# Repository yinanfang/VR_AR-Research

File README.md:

# VR_AR-Research
Code repo for VR_AR-Research

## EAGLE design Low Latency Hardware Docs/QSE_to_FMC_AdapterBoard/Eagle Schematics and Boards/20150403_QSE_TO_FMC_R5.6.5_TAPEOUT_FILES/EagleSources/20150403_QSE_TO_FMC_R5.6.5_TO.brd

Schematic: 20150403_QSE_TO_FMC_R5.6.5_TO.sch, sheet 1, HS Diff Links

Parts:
C100, C101: 100nF; CAPC1005X60N; PARTNO GRM155R71C104KA88D
H1, H2, H3, H4: MOUNT-PAD-ROUND3.2; 3,2-PAD; PARTNO *
J101_GBCTCLK1_N, J102-GBCTCLK1_P: SMA-SMD; MPN 132134-10; DIGIKEY_SKU 132134-10-ND
TP5: LOOP0_N; TP08R; PARTNO *
TP6: LOOP0_P; TP08R; PARTNO *
TP7, TP8: GND; TP08R; PARTNO *

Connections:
GBCTCLK1_M2C_C_N: C100.1 (2), J101_GBCTCLK1_N.1
GBCTCLK1_M2C_C_P: C101.1 (2), J102-GBCTCLK1_P.1
GBCTCLK1_M2C_N: C100.2 (1); also elsewhere on the board
GBCTCLK1_M2C_P: C101.2 (1); also elsewhere on the board
GND: H1.B3,2, H2.B3,2, H3.B3,2, H4.B3,2, J101_GBCTCLK1_N.2@1 (2), J101_GBCTCLK1_N.2@2 (2), J101_GBCTCLK1_N.2@3 (2), J101_GBCTCLK1_N.2@4 (2), J101_GBCTCLK1_N.2@5 (2), J101_GBCTCLK1_N.2@6 (2), J102-GBCTCLK1_P.2@1 (2), J102-GBCTCLK1_P.2@2 (2), J102-GBCTCLK1_P.2@3 (2), J102-GBCTCLK1_P.2@4 (2), J102-GBCTCLK1_P.2@5 (2), J102-GBCTCLK1_P.2@6 (2), TP7.TP, TP8.TP; also elsewhere on the board
LOOP0_N: TP5.TP; also elsewhere on the board
LOOP0_P: TP6.TP; also elsewhere on the board

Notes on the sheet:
3.2mm (1/4") mounting holes, tied to ground plane.
V7 Bank 37
V7 Bank 12
V7 Bank 38
V7 Bank 39
Low-speed (enable/detect)
High-speed Connectors
V7 Bank 111
QSE1/QSE2
Not Used
We only draw from the EXP2 3v3 power rail. The others are terminated to power planes and decoupled.
^ LVCMOS_18 ^
^ LVCMOS_18 ^ PULLUP
^ LVDS ^
V7 Bank 111 Optional external clock reference

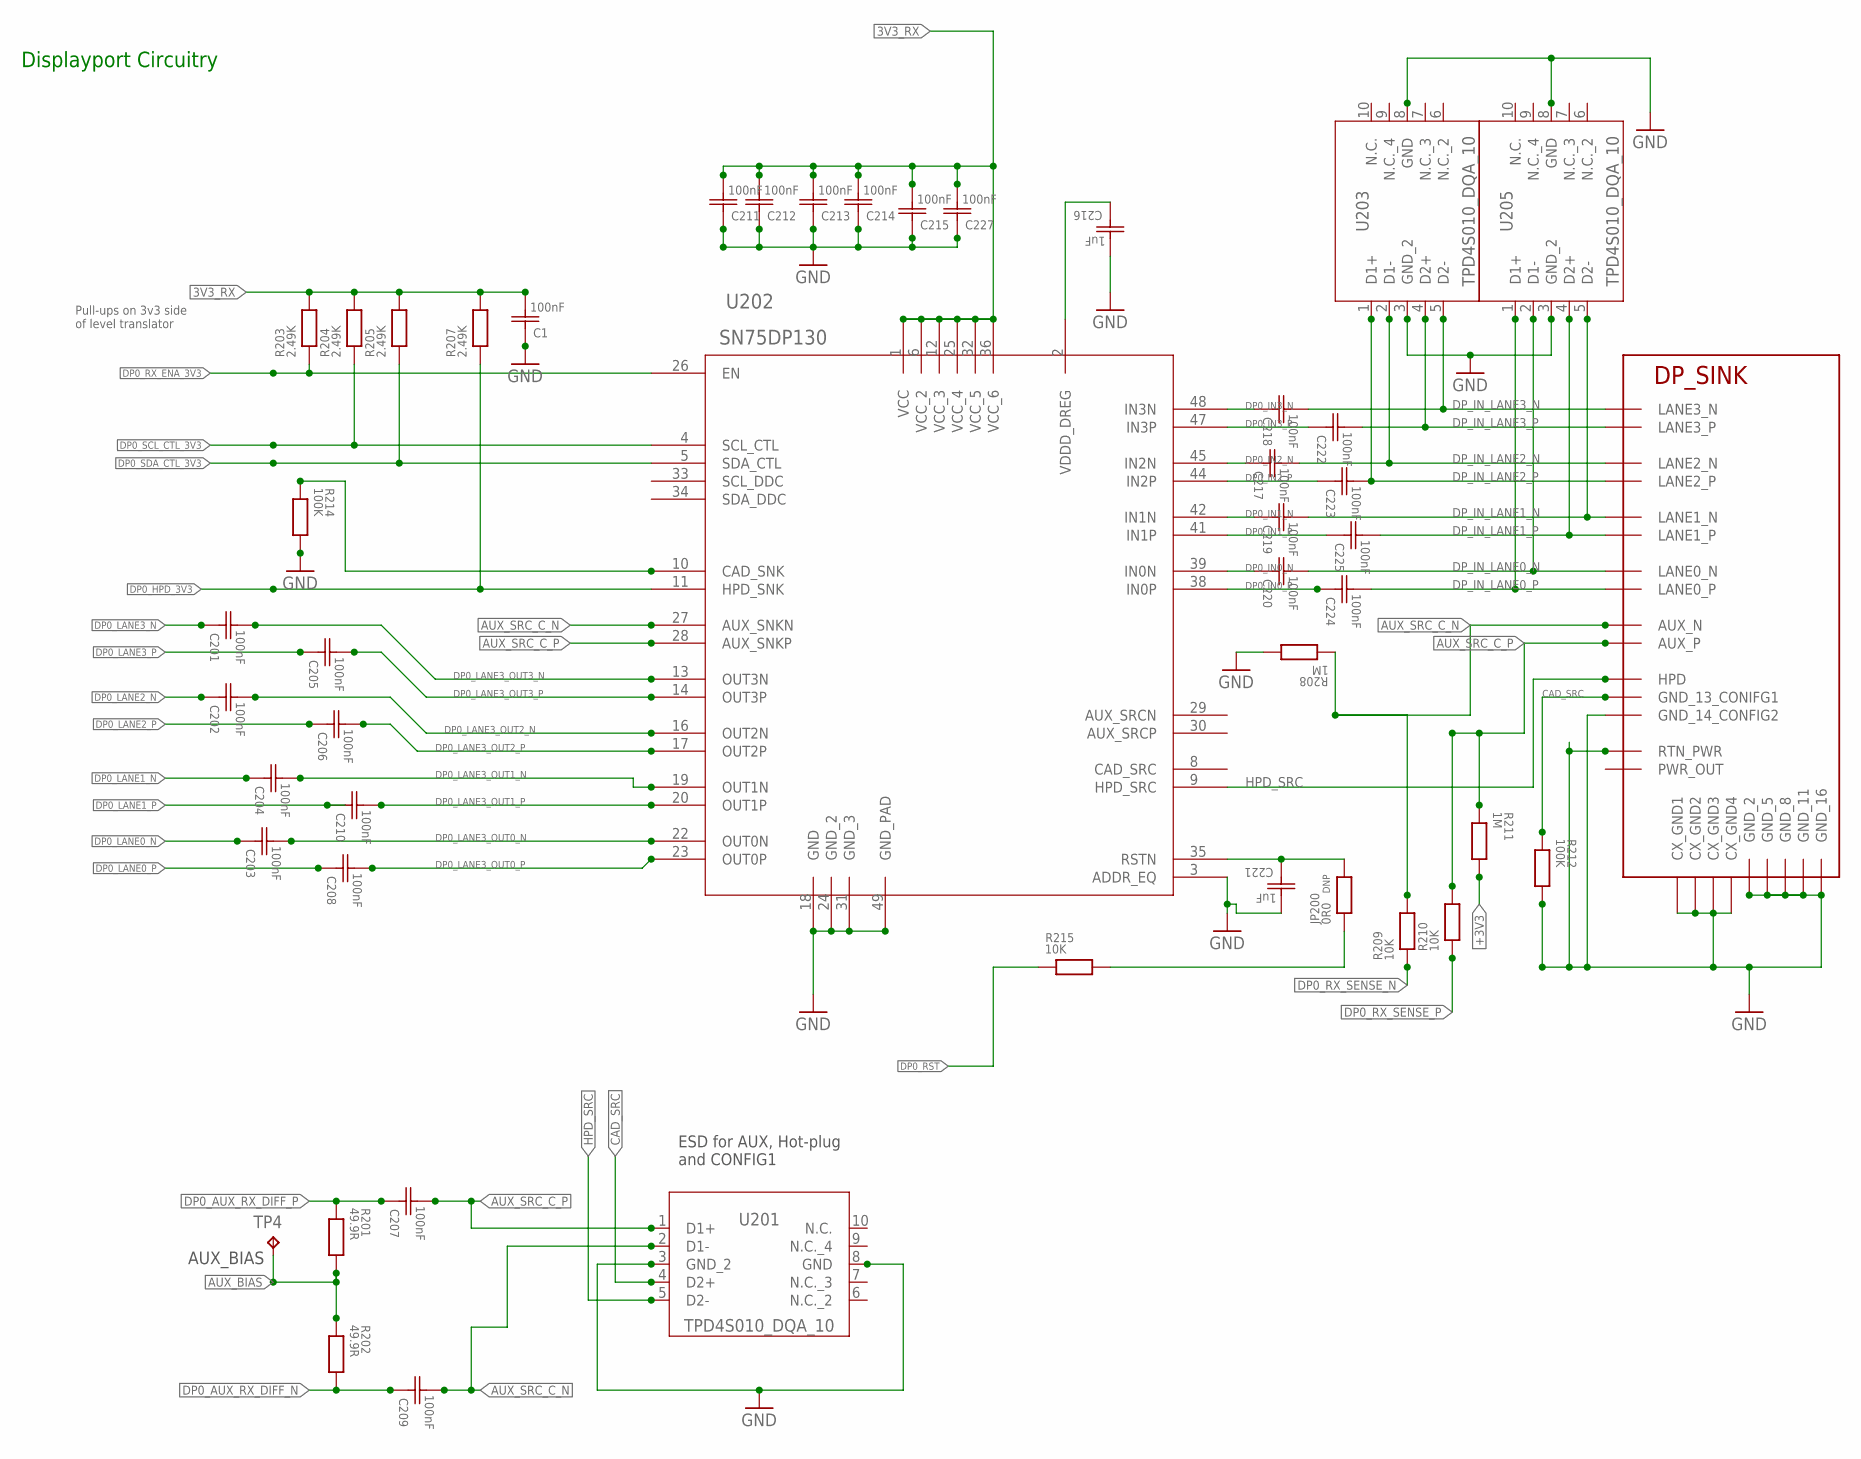
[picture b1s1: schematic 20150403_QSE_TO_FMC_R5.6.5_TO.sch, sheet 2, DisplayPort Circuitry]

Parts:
C1, C211, C212, C213, C214, C215, C227: 100nF; CAPC1005X60N; PART# GRM188B31H104MA92
C201, C202, C203, C204, C205, C206, C207, C208, C209, C210, C217, C218, C219, C220, C222, C223, C224, C225: 100nF; CAPC1005X60N; PARTNO GRM155R71C104KA88D
C216, C221: 1uF; CAPC1005X60N; PART# GRM188B31A225KE33
J200: DP0_IN; SD-47272; MPN 472700001
JP200: 0R0; RESC2013X65N; PARTNO DNP
R201, R202: 49.9R; RESC1005X40N; PARTNO TNPW040249R9BEED
R203, R204, R205, R207: 2.49K; RESC1005X40N; PARTNO CRCW04021K50FKED
R208, R211: 1M; RESC1005X40N; PARTNO CRCW04021M00DHEDP
R209, R210, R215: 10K; RESC1005X40N; PARTNO CRCW040210K0JNEDHP
R212, R214: 100K; RESC1005X40N; PARTNO CRCW0402100KFKED
TP4: AUX_BIAS; TP10R; PARTNO *
U201, U203, U205: TPD4S010_DQA_10; DQA10; MPN tpd4s010_dqa_10
U202: SN75DP130; RGZ48_5P6X5P6; MPN SN75DP130-SS

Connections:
3V3_RX: C1.1 (2), C211.1 (2), C212.1 (2), C213.1 (2), C214.1 (2), C215.1 (2), C227.1 (2), R203.1, R204.1, R205.1, R207.1, U202.1 (VCC), U202.6 (VCC_2), U202.12 (VCC_3), U202.25 (VCC_4), U202.32 (VCC_5), U202.36 (VCC_6); also elsewhere on the board
+3V3: R211.1; also elsewhere on the board
AUX_BIAS: R201.1, R202.2, TP4.TP; also elsewhere on the board
AUX_SRC_C_N: C209.1 (2), J200.P$17 (AUX_N), R208.2, R209.1, U201.2 (D1-), U202.27 (AUX_SNKN)
AUX_SRC_C_P: C207.1 (2), J200.P$15 (AUX_P), R210.1, R211.2, U201.1 (D1+), U202.28 (AUX_SNKP)
CAD_SNK_PULLDOWN: R214.2, U202.10 (CAD_SNK)
CAD_SRC: J200.P$13 (GND_13_CONIFG1), R212.2, U201.4 (D2+)
DP0_AUX_RX_DIFF_N: C209.2 (1), R202.1; also elsewhere on the board
DP0_AUX_RX_DIFF_P: C207.2 (1), R201.2; also elsewhere on the board
DP0_HPD_3V3: R207.2, U202.11 (HPD_SNK); also elsewhere on the board
DP0_IN0_N: C220.2 (1), U202.39 (IN0N)
DP0_IN0_P: C224.2 (1), U202.38 (IN0P)
DP0_IN1_N: C219.2 (1), U202.42 (IN1N)
DP0_IN1_P: C225.2 (1), U202.41 (IN1P)
DP0_IN2_N: C217.2 (1), U202.45 (IN2N)
DP0_IN2_P: C223.2 (1), U202.44 (IN2P)
DP0_IN3_N: C218.2 (1), U202.48 (IN3N)
DP0_IN3_P: C222.2 (1), U202.47 (IN3P)
DP0_LANE0_N: C203.2 (1); also elsewhere on the board
DP0_LANE0_P: C208.2 (1); also elsewhere on the board
DP0_LANE1_N: C204.2 (1); also elsewhere on the board
DP0_LANE1_P: C210.2 (1); also elsewhere on the board
DP0_LANE2_N: C202.2 (1); also elsewhere on the board
DP0_LANE2_P: C206.2 (1); also elsewhere on the board
DP0_LANE3_N: C201.2 (1); also elsewhere on the board
DP0_LANE3_OUT0_N: C203.1 (2), U202.22 (OUT0N)
DP0_LANE3_OUT0_P: C208.1 (2), U202.23 (OUT0P)
DP0_LANE3_OUT1_N: C204.1 (2), U202.19 (OUT1N)
DP0_LANE3_OUT1_P: C210.1 (2), U202.20 (OUT1P)
DP0_LANE3_OUT2_N: C202.1 (2), U202.16 (OUT2N)
DP0_LANE3_OUT2_P: C206.1 (2), U202.17 (OUT2P)
DP0_LANE3_OUT3_N: C201.1 (2), U202.13 (OUT3N)
DP0_LANE3_OUT3_P: C205.1 (2), U202.14 (OUT3P)
DP0_LANE3_P: C205.2 (1); also elsewhere on the board
DP0_RST: R215.2; also elsewhere on the board
DP0_RST_CONTROL: JP200.2, R215.1
DP0_RX_ENA_3V3: R203.2, U202.26 (EN); also elsewhere on the board
DP0_RX_SENSE_N: R209.2; also elsewhere on the board
DP0_RX_SENSE_P: R210.2; also elsewhere on the board
DP0_SCL_CTL_3V3: R204.2, U202.4 (SCL_CTL); also elsewhere on the board
DP0_SDA_CTL_3V3: R205.2, U202.5 (SDA_CTL); also elsewhere on the board
DP_IN_LANE0_N: C220.1 (2), J200.P$10 (LANE0_N), U205.2 (D1-)
DP_IN_LANE0_P: C224.1 (2), J200.P$12 (LANE0_P), U205.1 (D1+)
DP_IN_LANE1_N: C219.1 (2), J200.P$7 (LANE1_N), U205.5 (D2-)
DP_IN_LANE1_P: C225.1 (2), J200.P$9 (LANE1_P), U205.4 (D2+)
DP_IN_LANE2_N: C217.1 (2), J200.P$4 (LANE2_N), U203.2 (D1-)
DP_IN_LANE2_P: C223.1 (2), J200.P$6 (LANE2_P), U203.1 (D1+)
DP_IN_LANE3_N: C218.1 (2), J200.P$1 (LANE3_N), U203.5 (D2-)
DP_IN_LANE3_P: C222.1 (2), J200.P$3 (LANE3_P), U203.4 (D2+)
GND: C1.2 (1), C211.2 (1), C212.2 (1), C213.2 (1), C214.2 (1), C215.2 (1), C216.1 (2), C221.1 (2), C227.2 (1), J200.P$2 (GND_2), J200.P$5 (GND_5), J200.P$8 (GND_8), J200.P$11 (GND_11), J200.P$14 (GND_14_CONFIG2), J200.P$16 (GND_16), J200.P$19 (RTN_PWR), J200.P$21 (CX_GND1), J200.P$22 (CX_GND2), J200.P$23 (CX_GND3), J200.P$24 (CX_GND4), R208.1, R212.1, R214.1, U201.3 (GND_2), U201.8 (GND), U202.3 (ADDR_EQ), U202.18 (GND), U202.24 (GND_2), U202.31 (GND_3), U202.49 (GND_PAD), U203.3 (GND_2), U203.8 (GND), U205.3 (GND_2), U205.8 (GND); also elsewhere on the board
HPD_SRC: J200.P$18 (HPD), U201.5 (D2-), U202.9 (HPD_SRC)
PWR_OUT: J200.P$20 (PWR_OUT)
RSTN_SOFT_START: C221.2 (1), JP200.1, U202.35 (RSTN)
VDDD_DREG_DECOUPLE: C216.2 (1), U202.2 (VDDD_DREG)

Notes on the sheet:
ESD for AUX, Hot-plug and CONFIG1
Displayport Circuitry
Pull-ups on 3v3 side of level translator

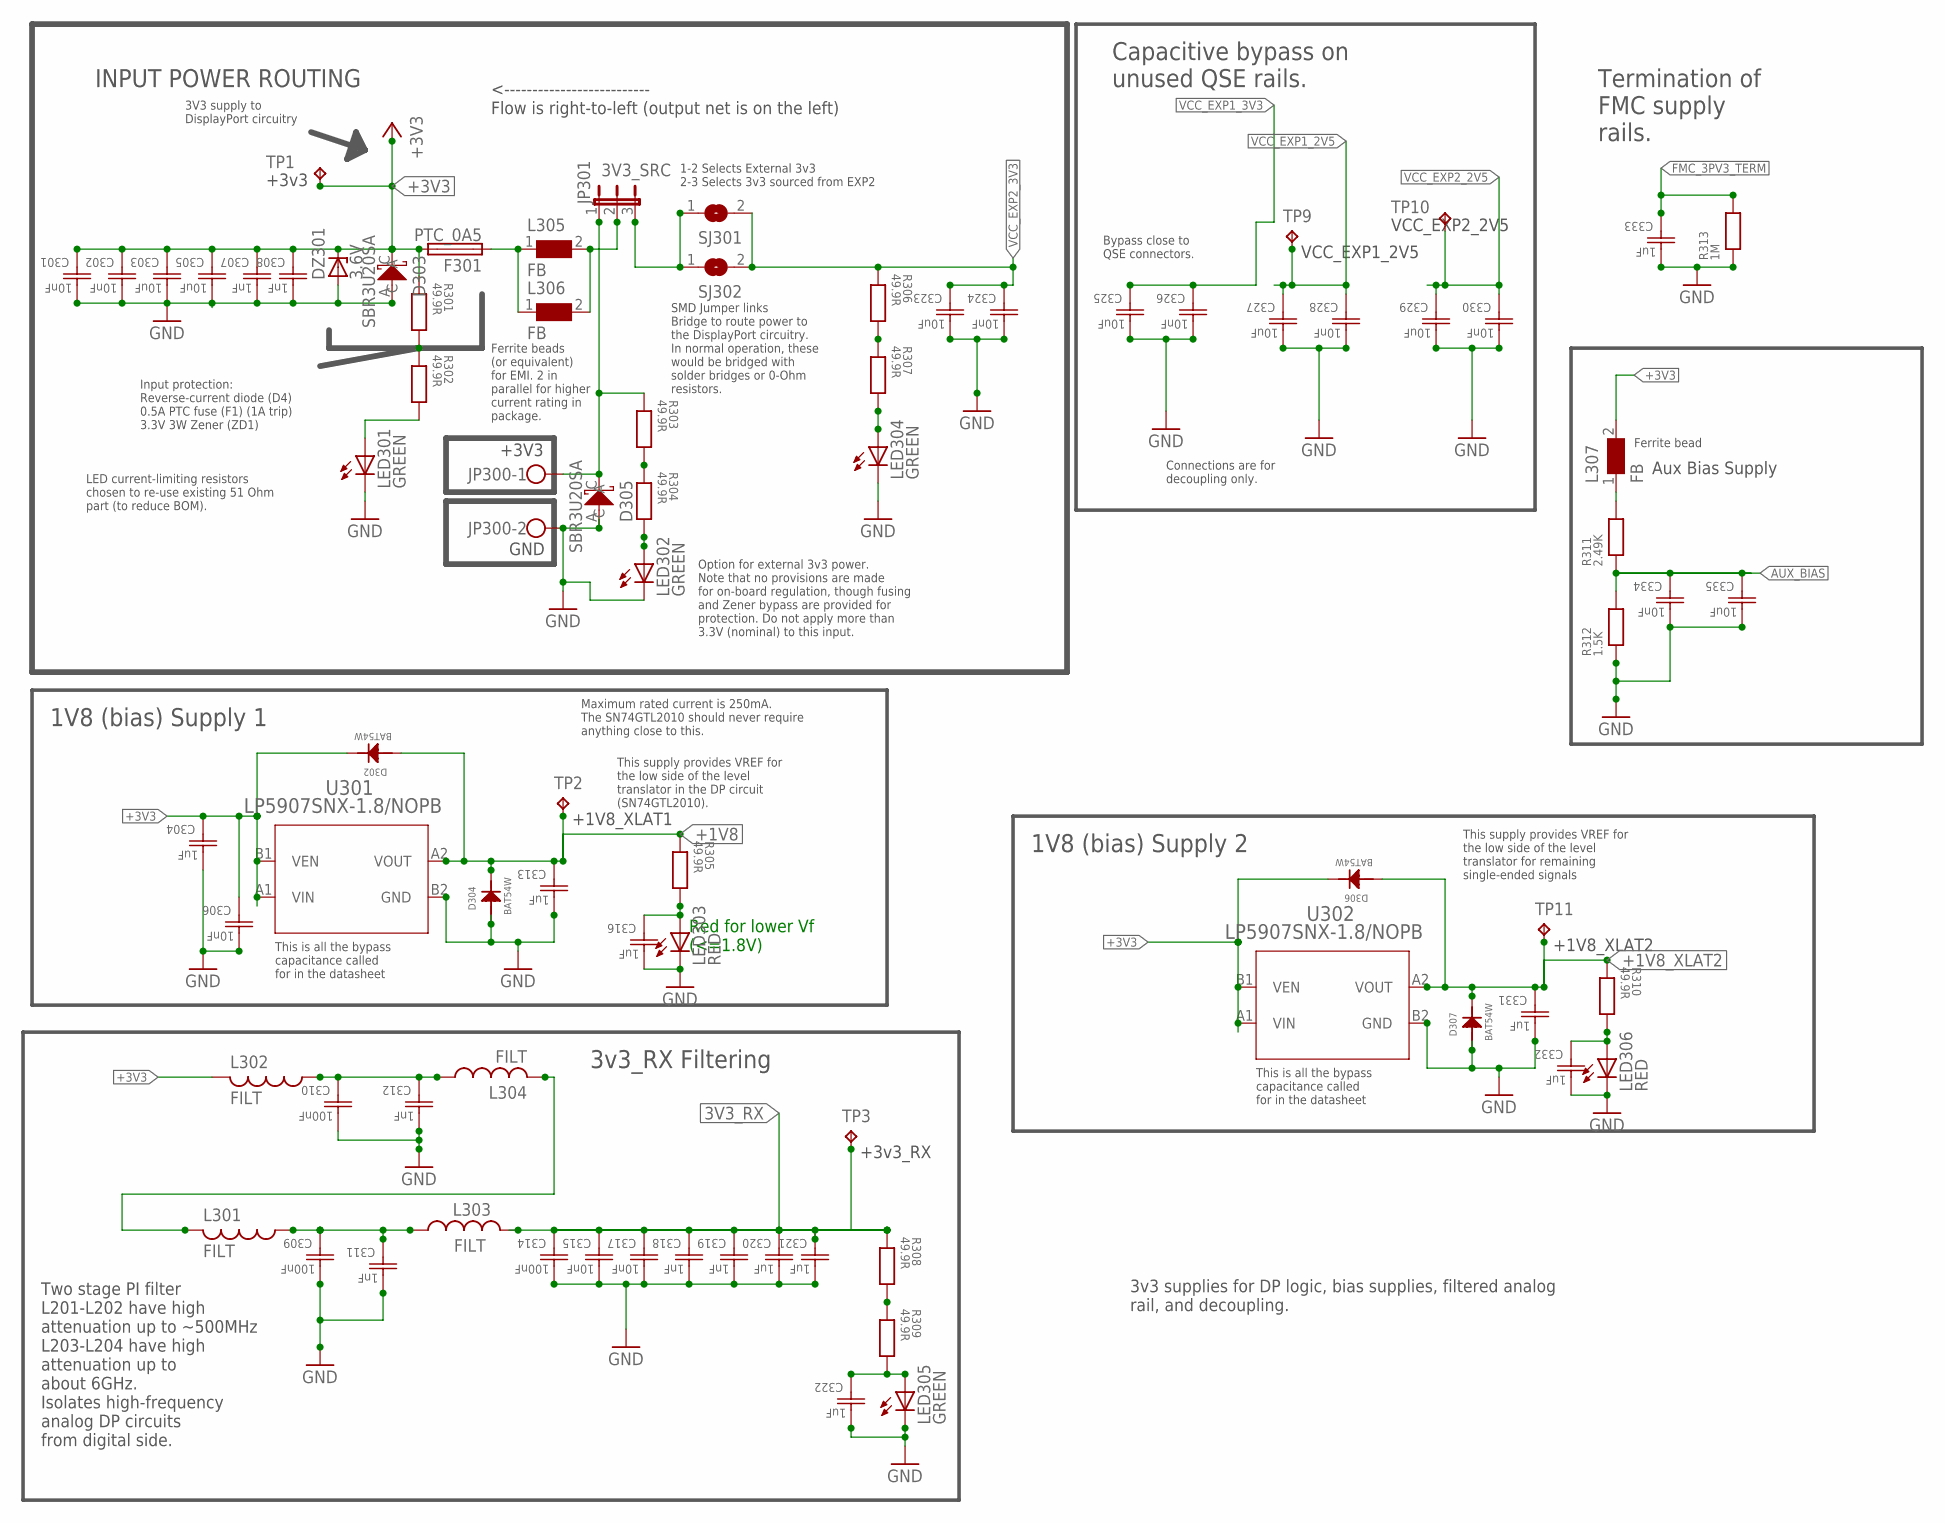
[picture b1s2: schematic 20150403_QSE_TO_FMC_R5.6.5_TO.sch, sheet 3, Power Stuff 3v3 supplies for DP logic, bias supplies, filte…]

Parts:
C301, C302, C324, C326, C328, C330: 10nF; CAPC1005X60N; PARTNO GRM155R71E103KA01D
C303, C305, C323, C325, C327, C329, C335: 10uF; CAPC1608X85N; PARTNO GRM188R60J106ME47D
C304, C313, C331: 1uF; CAPC1005X60N; PARTNO GRM155R61A105KE15D
C306, C315, C317, C334: 10nF; CAPC1005X60N; PART# GRM1885C1H103JA01
C307, C308, C311, C312, C318, C319: 1nF; CAPC1005X60N; PART# GRM1885C1E102JA01
C309, C310, C314: 100nF; CAPC1005X60N; PART# GRM188B31H104MA92
C316, C320, C321, C322, C332, C333: 1uF; CAPC1005X60N; PART# GRM188B31A225KE33
D302, D304, D306, D307: BAT54W; SOT65P210X100-3N; PARTNO BAT54W-7-F
D303, D305: SBR3U20SA; SMA; MPN SBR3U20SA-13
DZ301: 3.6V; SMB; MPN 1SMB5914BT3G
F301: PTC_0A5; SMD-0805; MPN MF-PSMF050X
JP300: W237-102; PARTNO 395443002
JP301: 3V3_SRC; JP2; PARTNO 901200763
L301, L303: FILT; R0603; MPN BLM18HE601SN1
L302, L304: FILT; R0603; MPN BLM18HE152SN1
L305, L306: FB; 0805; PARTNO 742792097
L307: FB; 0402; PARTNO 742841210
LED301, LED302, LED304: GREEN; CHIP-LED0805; MPN LG R971-KN-1; DIGIKEY_SKU 475-1410-1-ND
LED303, LED306: RED; SML0603; MPN 5975112407F; DIGIKEY_SKU 350-2436-6-ND
LED305: GREEN; CHIP-LED0805; PART# LG R971-KN-1; DIGIKEY_SKU 475-1410-1-ND
R301, R302, R303, R304, R305, R306, R307, R308, R309, R310: 49.9R; RESC1005X40N; PARTNO TNPW040249R9BEED
R311: 2.49K; RESC1005X40N; PARTNO CRCW04022K49FKED
R312: 1.5K; RESC1005X40N; PARTNO CRCW04021K50FKED
R313: 1M; RESC1005X40N; PARTNO CRCW04021M00DHEDP
SJ301, SJ302: SJW; PARTNO *
TP1: +3v3; TP10R; PARTNO *
TP2: +1V8_XLAT1; TP10R
TP3: +3v3_RX; TP10R; PARTNO *
TP9: VCC_EXP1_2V5; TP07R; PARTNO *
TP10: VCC_EXP2_2V5; TP07R; PARTNO *
TP11: +1V8_XLAT2; TP10R
U301, U302: LP5907SNX-1.8/NOPB; YKE4; PARTNO LP5907SNX-1.8/NOPB

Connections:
1V8_LED: C316.2 (1), LED303.A, R305.1
1V8_LED1: C332.2 (1), LED306.A, R310.1
3V3_EXP_JP: D305.C, JP300.1, JP301.1, R303.2
3V3_INT_JP: JP301.3, SJ301.1, SJ302.1
3V3_INT_LED: LED304.A, R307.1
3V3_IN_FILTER_TO_FUSE: F301.1, L305.1, L306.1
3V3_RX: C314.2 (1), C315.2 (1), C317.2 (1), C318.2 (1), C319.2 (1), C320.2 (1), C321.2 (1), L303.2, R308.2, TP3.TP; also elsewhere on the board
3V3_RX_FILT_S0: C310.2 (1), C312.2 (1), L302.1, L304.1
3V3_RX_FILT_S1: L301.2, L304.2
3V3_RX_FILT_S2: C309.2 (1), C311.2 (1), L301.1, L303.1
3V3_RX_LED: C322.2 (1), LED305.A, R309.1
3V3_TO_AUX_BIAS_POST_FILTER: L307.1, R311.1
+1V8: C313.2 (1), D302.1 (A), D304.3 (C), R305.2, TP2.TP, U301.A2 (VOUT); also elsewhere on the board
+1V8_XLAT2: C331.2 (1), D306.1 (A), D307.3 (C), R310.2, TP11.TP, U302.A2 (VOUT); also elsewhere on the board
+3V3: C301.2 (1), C302.2 (1), C303.2 (1), C304.2 (1), C305.2 (1), C306.2 (1), C307.2 (1), C308.2 (1), D302.3 (C), D303.C, D306.3 (C), DZ301.C, F301.2, L302.2, L307.2, R301.2, TP1.TP, U301.A1 (VIN), U301.B1 (VEN), U302.A1 (VIN), U302.B1 (VEN); also elsewhere on the board
AUX_BIAS: C334.2 (1), C335.2 (1), R311.2, R312.1; also elsewhere on the board
EXT_3V3_LED: LED302.A, R304.1
FMC_3PV3_TERM: C333.2 (1), R313.1; also elsewhere on the board
GND: C301.1 (2), C302.1 (2), C303.1 (2), C304.1 (2), C305.1 (2), C306.1 (2), C307.1 (2), C308.1 (2), C309.1 (2), C310.1 (2), C311.1 (2), C312.1 (2), C313.1 (2), C314.1 (2), C315.1 (2), C316.1 (2), C317.1 (2), C318.1 (2), C319.1 (2), C320.1 (2), C321.1 (2), C322.1 (2), C323.1 (2), C324.1 (2), C325.1 (2), C326.1 (2), C327.1 (2), C328.1 (2), C329.1 (2), C330.1 (2), C331.1 (2), C332.1 (2), C333.1 (2), C334.1 (2), C335.1 (2), D303.A, D304.1 (A), D305.A, D307.1 (A), DZ301.A, JP300.2, LED301.C, LED302.C, LED303.C, LED304.C, LED305.C, LED306.C, R312.2, R313.2, U301.B2 (GND), U302.B2 (GND); also elsewhere on the board
MAIN_POWER_LED: LED301.A, R302.1
R303_R304: R301.1, R302.2
R306_R305: R303.1, R304.2
R308_R307: R306.1, R307.2
R309_R310: R308.1, R309.2
SELECTED_3V3: JP301.2, L305.2, L306.2
VCC_EXP1_2V5: C327.2 (1), C328.2 (1), TP9.TP; also elsewhere on the board
VCC_EXP1_3V3: C325.2 (1), C326.2 (1); also elsewhere on the board
VCC_EXP2_2V5: C329.2 (1), C330.2 (1), TP10.TP; also elsewhere on the board
VCC_EXP2_3V3: C323.2 (1), C324.2 (1), R306.2, SJ301.2, SJ302.2; also elsewhere on the board

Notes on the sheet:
This supply provides VREF for the low side of the level translator in the DP circuit (SN74GTL2010).
Aux Bias Supply
1-2 Selects External 3v3 2-3 Selects 3v3 sourced from EXP2
INPUT POWER ROUTING
SMD Jumper links Bridge to route power to the DisplayPort circuitry. In normal operation, these would be bridged with solder bridges or 0-Ohm resistors.
+3V3
GND
Option for external 3v3 power. Note that no provisions are made for on-board regulation, though fusing and Zener bypass are provided for protection. Do not apply more than 3.3V (nominal) to this input.
Input protection: Reverse-current diode (D4) 0.5A PTC fuse (F1) (1A trip) 3.3V 3W Zener (ZD1)
3V3 supply to DisplayPort circuitry
Bypass close to QSE connectors.
Two stage PI filter L201-L202 have high attenuation up to ~500MHz L203-L204 have high attenuation up to about 6GHz. Isolates high-frequency analog DP circuits from digital side.
Maximum rated current is 250mA. The SN74GTL2010 should never require anything close to this.
This is all the bypass capacitance called for in the datasheet
3v3_RX Filtering
1V8 (bias) Supply 1
Red for lower Vf (<=1.8V)
Connections are for decoupling only.
Ferrite beads (or equivalent) for EMI. 2 in parallel for higher current rating in package.
LED current-limiting resistors chosen to re-use existing 51 Ohm part (to reduce BOM).
<-------------------------- Flow is right-to-left (output net is on the left)
Ferrite bead
Capacitive bypass on unused QSE rails.
3v3 supplies for DP logic, bias supplies, filtered analog rail, and decoupling.
Termination of FMC supply rails.
This supply provides VREF for the low side of the level translator for remaining single-ended signals
1V8 (bias) Supply 2

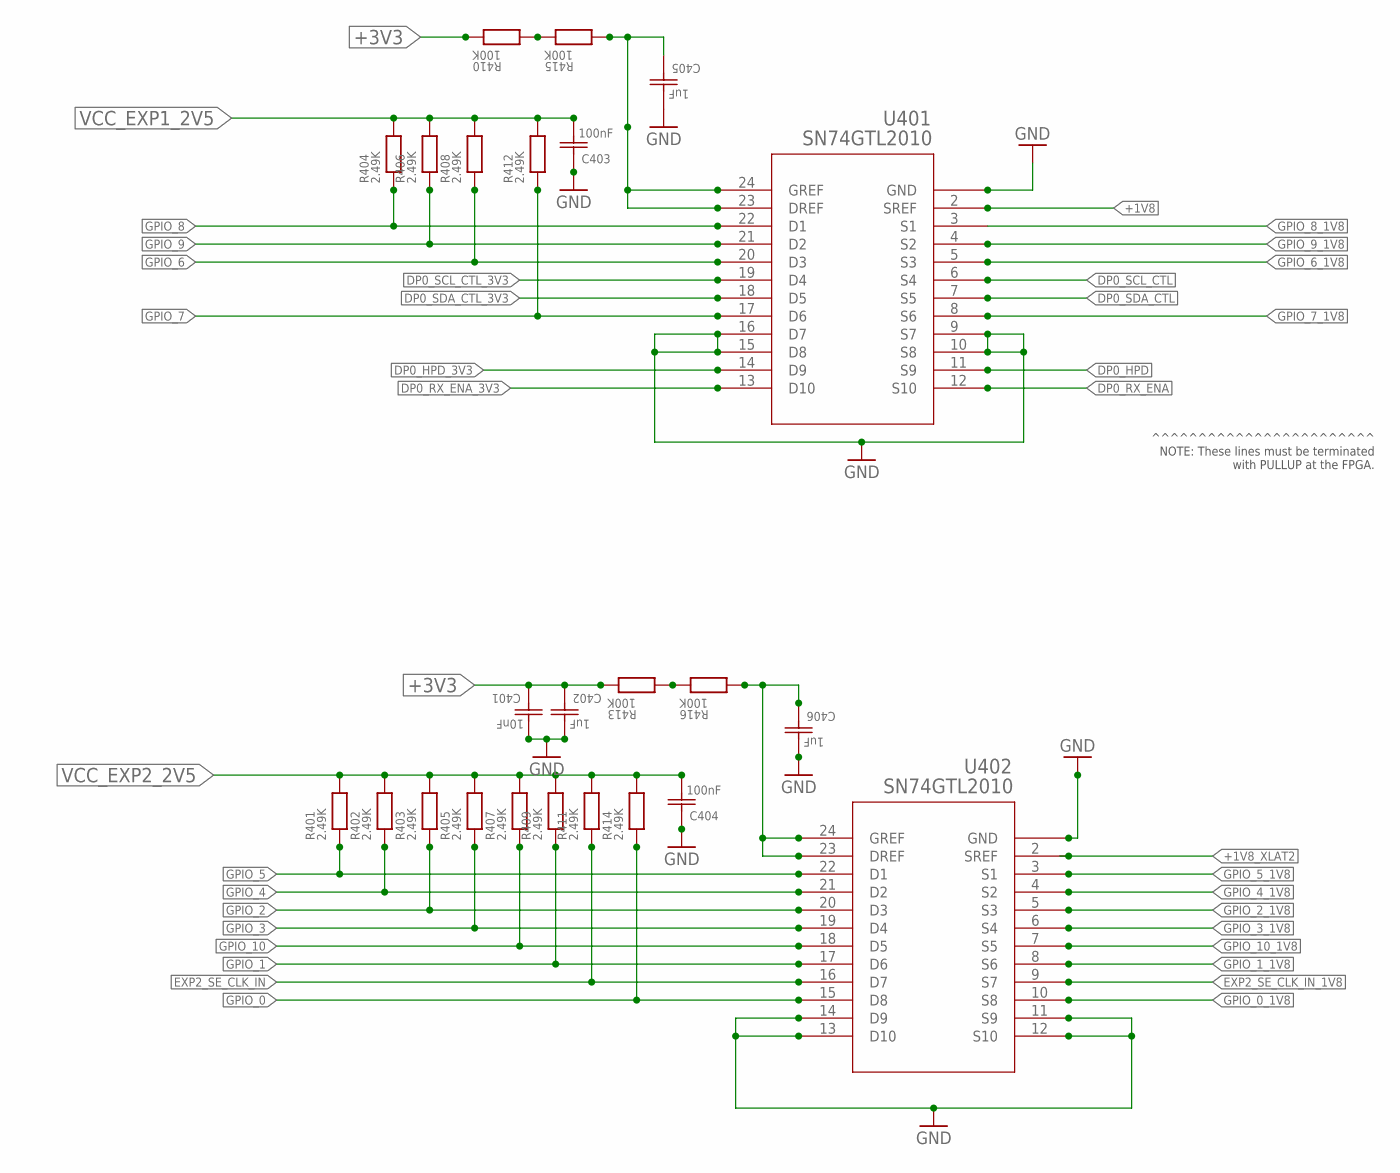
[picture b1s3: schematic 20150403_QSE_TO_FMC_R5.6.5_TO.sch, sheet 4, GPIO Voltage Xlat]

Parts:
C401: 10nF; CAPC1005X60N; PARTNO GRM155R71E103KA01D
C402, C405, C406: 1uF; CAPC1005X60N; PART# GRM188B31A225KE33
C403, C404: 100nF; CAPC1005X60N; PART# GRM188B31H104MA92
R401, R402, R403, R404, R405, R406, R407, R408, R409, R411, R412, R414: 2.49K; RESC1005X40N; PARTNO CRCW04021K50FKED
R410, R413, R415, R416: 100K; RESC1005X40N; PARTNO CRCW0402100KFKED
U401, U402: SN74GTL2010; PW24; MPN sn74gtl2010_pw_24

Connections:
+1V8: U401.2 (SREF); also elsewhere on the board
+1V8_XLAT2: U402.2 (SREF); also elsewhere on the board
+3V3: C401.2 (1), C402.2 (1), R410.2, R413.2; also elsewhere on the board
DP0_HPD: U401.11 (S9); also elsewhere on the board
DP0_HPD_3V3: U401.14 (D9); also elsewhere on the board
DP0_RX_ENA: U401.12 (S10); also elsewhere on the board
DP0_RX_ENA_3V3: U401.13 (D10); also elsewhere on the board
DP0_SCL_CTL: U401.6 (S4); also elsewhere on the board
DP0_SCL_CTL_3V3: U401.19 (D4); also elsewhere on the board
DP0_SDA_CTL: U401.7 (S5); also elsewhere on the board
DP0_SDA_CTL_3V3: U401.18 (D5); also elsewhere on the board
EXP2_SE_CLK_IN: R411.2, U402.16 (D7); also elsewhere on the board
EXP2_SE_CLK_IN_1V8: U402.9 (S7); also elsewhere on the board
GND: C401.1 (2), C402.1 (2), C403.2 (1), C404.2 (1), C405.1 (2), C406.1 (2), U401.1 (GND), U401.9 (S7), U401.10 (S8), U401.15 (D8), U401.16 (D7), U402.1 (GND), U402.11 (S9), U402.12 (S10), U402.13 (D10), U402.14 (D9); also elsewhere on the board
GPIO_0: R414.2, U402.15 (D8); also elsewhere on the board
GPIO_0_1V8: U402.10 (S8); also elsewhere on the board
GPIO_1: R409.2, U402.17 (D6); also elsewhere on the board
GPIO_1_1V8: U402.8 (S6); also elsewhere on the board
GPIO_2: R403.2, U402.20 (D3); also elsewhere on the board
GPIO_2_1V8: U402.5 (S3); also elsewhere on the board
GPIO_3: R405.2, U402.19 (D4); also elsewhere on the board
GPIO_3_1V8: U402.6 (S4); also elsewhere on the board
GPIO_4: R402.2, U402.21 (D2); also elsewhere on the board
GPIO_4_1V8: U402.4 (S2); also elsewhere on the board
GPIO_5: R401.2, U402.22 (D1); also elsewhere on the board
GPIO_5_1V8: U402.3 (S1); also elsewhere on the board
GPIO_6: R408.2, U401.20 (D3); also elsewhere on the board
GPIO_6_1V8: U401.5 (S3); also elsewhere on the board
GPIO_7: R412.2, U401.17 (D6); also elsewhere on the board
GPIO_7_1V8: U401.8 (S6); also elsewhere on the board
GPIO_8: R404.2, U401.22 (D1); also elsewhere on the board
GPIO_8_1V8: U401.3 (S1); also elsewhere on the board
GPIO_9: R406.2, U401.21 (D2); also elsewhere on the board
GPIO_9_1V8: U401.4 (S2); also elsewhere on the board
GPIO_10: R407.2, U402.18 (D5); also elsewhere on the board
GPIO_10_1V8: U402.7 (S5); also elsewhere on the board
unnamed: R413.1, R416.2
unnamed: R410.1, R415.2
VCC_EXP1_2V5: C403.1 (2), R404.1, R406.1, R408.1, R412.1; also elsewhere on the board
VCC_EXP2_2V5: C404.1 (2), R401.1, R402.1, R403.1, R405.1, R407.1, R409.1, R411.1, R414.1; also elsewhere on the board
XLAT01_3V3_BIAS: C405.2 (1), R415.1, U401.23 (DREF), U401.24 (GREF)
XLAT02_3V3_BIAS: C406.2 (1), R416.1, U402.23 (DREF), U402.24 (GREF)

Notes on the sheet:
^^^^^^^^^^^^^^^^^^^^^^^^ NOTE: These lines must be terminated with PULLUP at the FPGA.

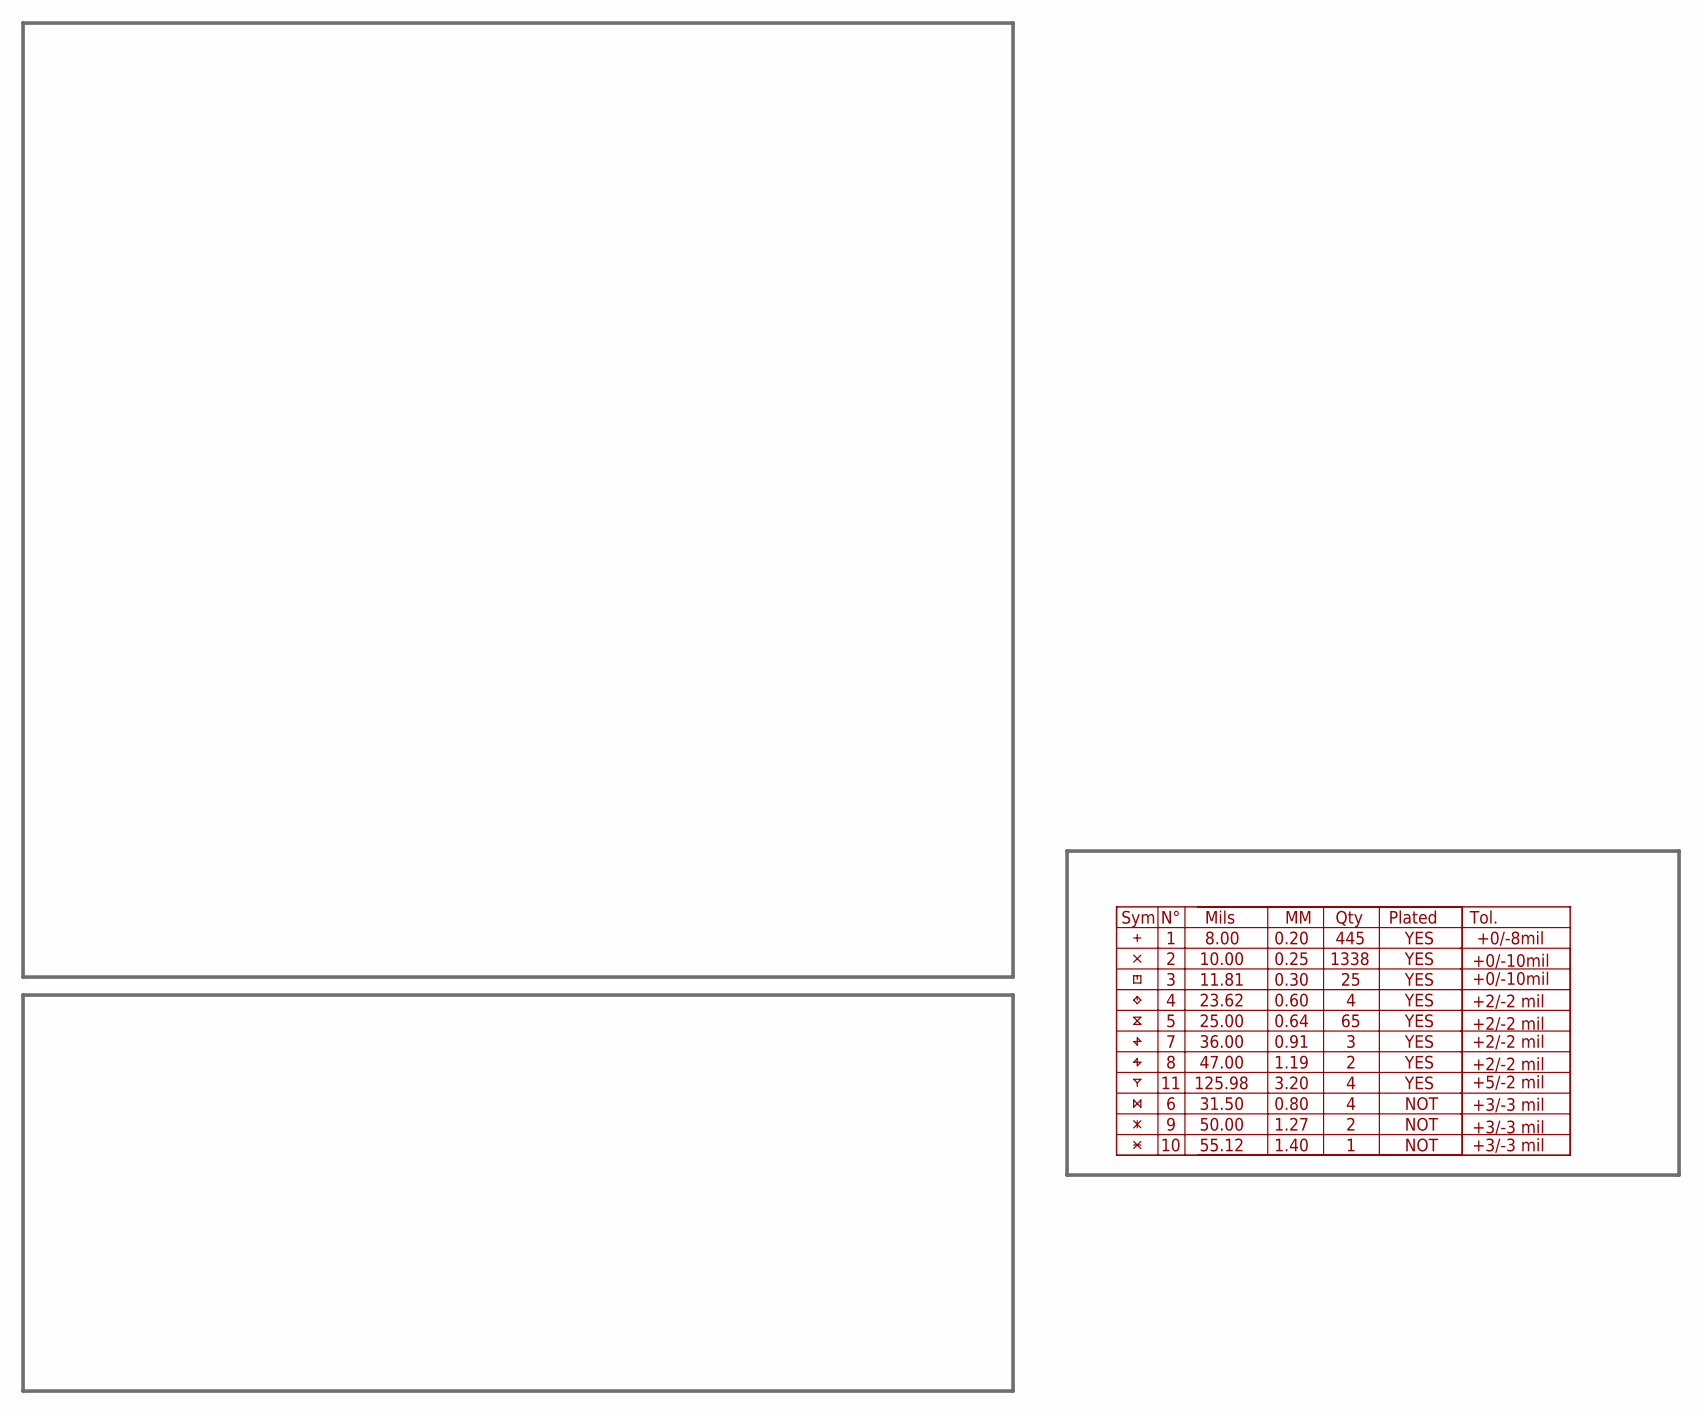
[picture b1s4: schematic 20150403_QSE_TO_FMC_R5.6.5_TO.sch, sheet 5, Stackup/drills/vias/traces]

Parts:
U$1: DRILEGENDDRILEGEND; DRILEGEND

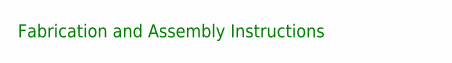
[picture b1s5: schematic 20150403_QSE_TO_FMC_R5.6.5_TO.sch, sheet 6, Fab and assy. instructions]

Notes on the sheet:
Fabrication and Assembly Instructions

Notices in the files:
Low Latency Hardware Docs/QSE_to_FMC_AdapterBoard/Eagle Schematics and Boards/20150104_QSE_to_FMC_6Layer_R3.1/20150104_QSE_to_FMC_6Layer_R3.1.brd:
Copyright (C) 2015. All Rights Reserved.
Low Latency Hardware Docs/QSE_to_FMC_AdapterBoard/Eagle Schematics and Boards/20150403_QSE_TO_FMC_R5.6.5_TAPEOUT_FILES/EagleSources/20150403_QSE_TO_FMC_R5.6.5_TO.brd:
Copyright (C) 2015 Alex Blate
